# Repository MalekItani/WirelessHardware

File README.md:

# Wireless Hardware
Welcome to the repository containing the circuit design files for wireless earbuds! In this repository, you will find all the necessary files to create your own wireless earbuds, including schematics, PCB layouts, and bill of materials.

## Software Dependencies/Requirements

- Kicad version 4.0 or greater.

## Repository Contents
This repository contains the following directories:

**Schematics**: Detailed diagrams of the circuitry used in the wireless earbuds.

**PCB layouts**: Physical layouts of the printed circuit board used in the wireless earbuds.

**Bill of materials**: A list of components and materials needed to build the wireless earbuds.

## Getting Started
To use these circuit design files, follow the steps below:

#### 1. Install KiCad: 
Download and install KiCad version 4.0 or greater from the official website. Choose the appropriate version for your operating system.

#### 2. Customize and Optimize: 
Import the schematics and PCB layouts into KiCad to begin customizing and optimizing the design to fit your specific needs. For detailed instructions on using KiCad, consult the official documentation.

## Firmware
The repository containing the firmware is located here: [https://github.com/antoniog11/OAEbud-firmware](https://github.com/antoniog11/OAEbud-firmware/)

## License
This repository is licensed under the MIT License. You are free to use and modify the circuit design files in any way you see fit, as long as you include the appropriate attribution and comply with the terms of the license.

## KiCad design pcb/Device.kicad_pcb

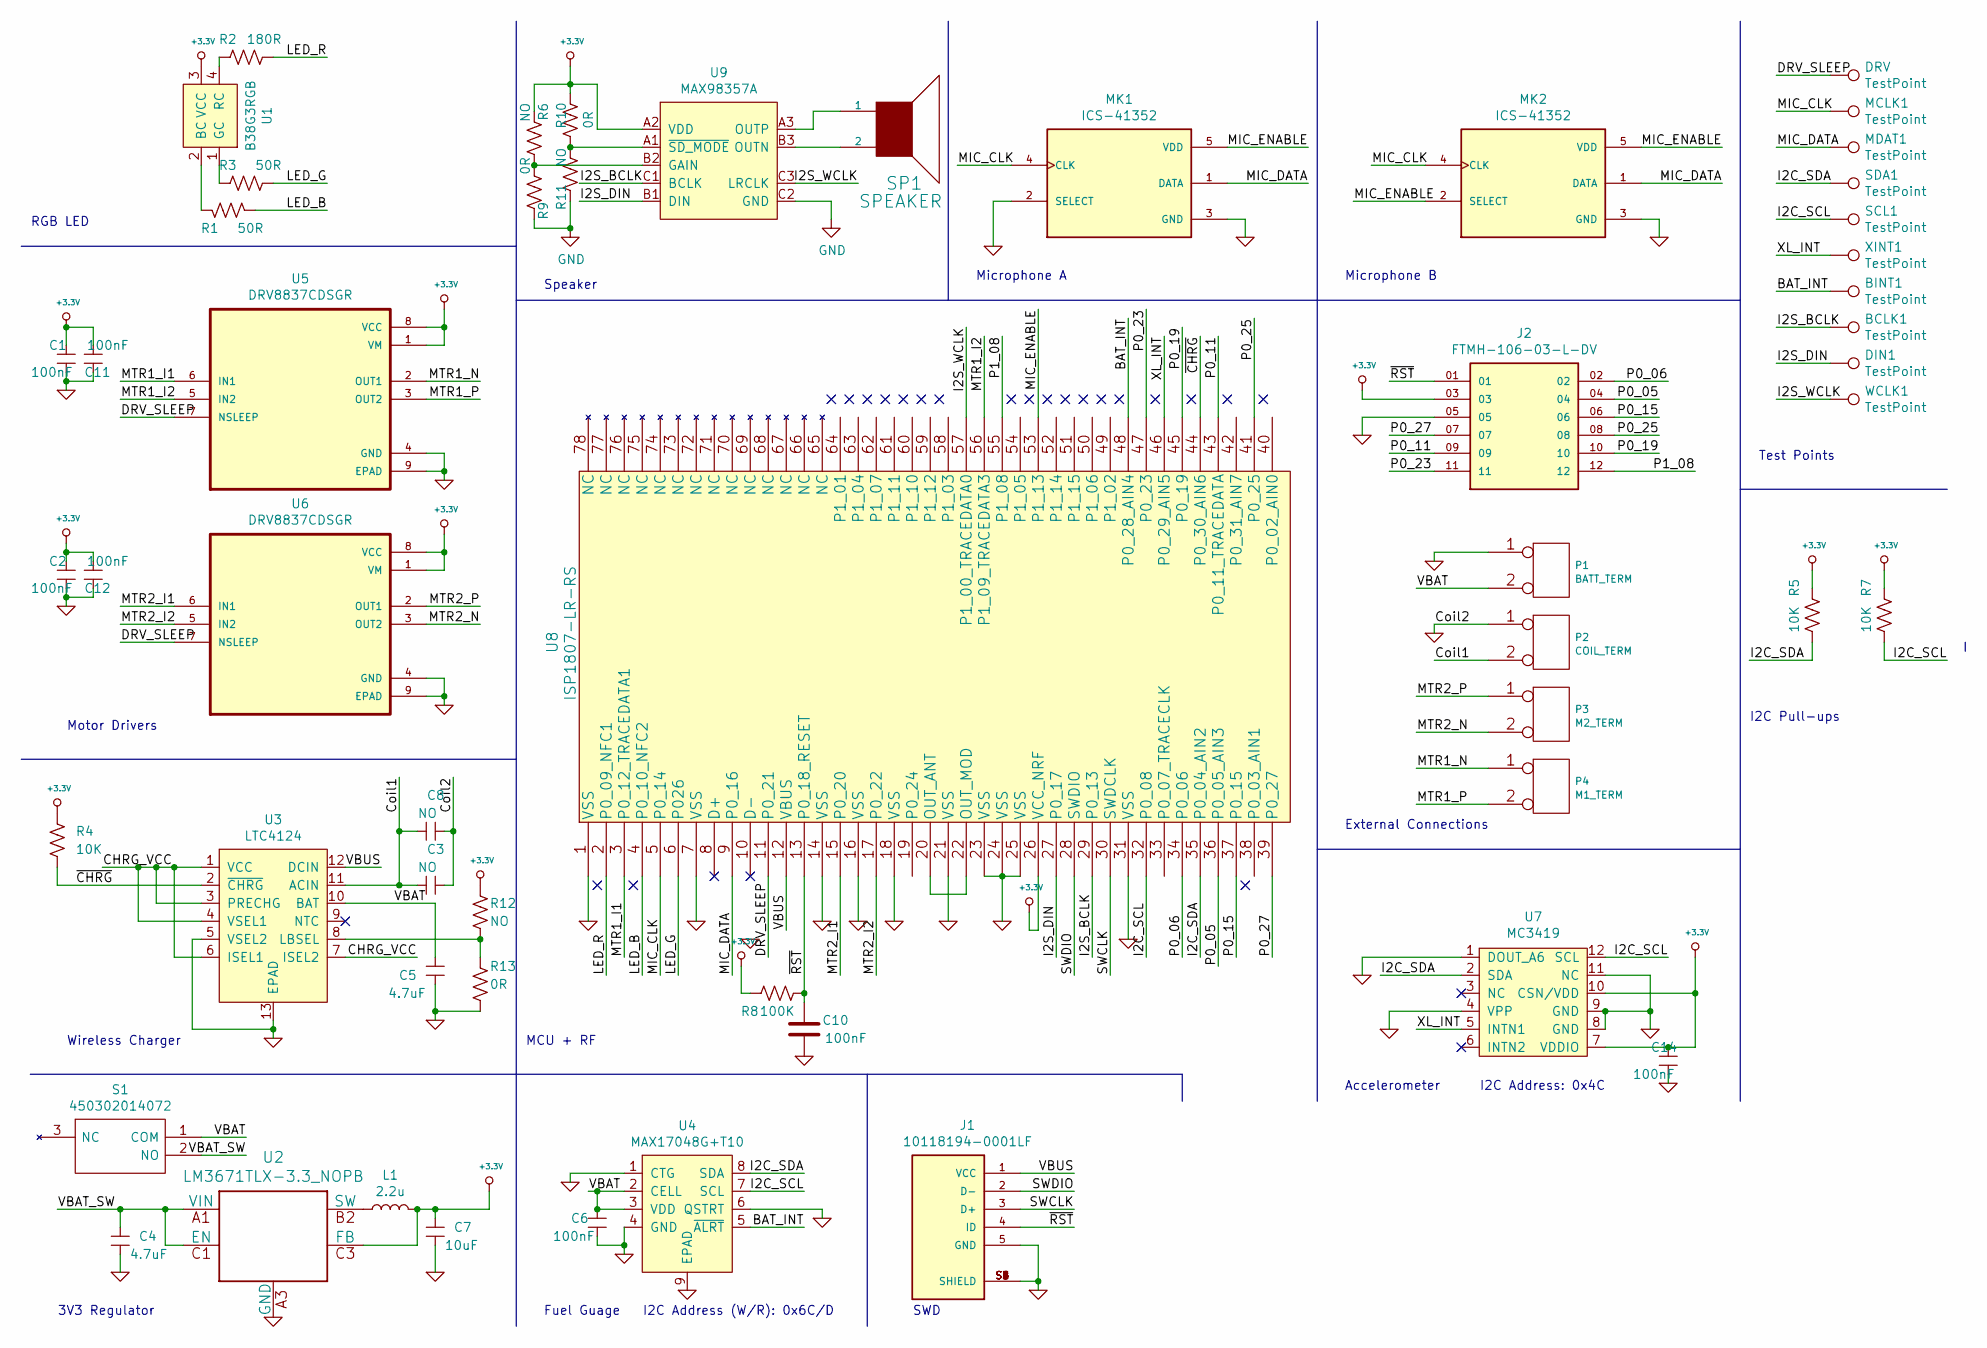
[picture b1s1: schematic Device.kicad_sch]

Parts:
BCLK1: TestPoint; TestPoint_Pad_D1.0mm
BINT1: TestPoint; TestPoint_Pad_D1.0mm
C1, C2, C6, C10, C11, C12, C14: 100nF; C_0402_1005Metric
C3, C8: NO; C_0402_1005Metric
C4, C5: 4.7uF; C_0603_1608Metric
C7: 10uF; C_0603_1608Metric
DIN1: TestPoint; TestPoint_Pad_D1.0mm
DRV: TestPoint; TestPoint_Pad_D1.0mm
J1: 10118194-0001LF; AMPHENOL_10118194-0001LF; PARTREV B
J2: FTMH-106-03-L-DV; SAMTEC_FTMH-106-03-L-DV; Manufacturer P/N FTMH-106-03-L-DV
L1: 2.2u; L_0805_2012Metric; Manufacturer P/N DFE201210U-2R2M=P2
MCLK1: TestPoint; TestPoint_Pad_D1.0mm
MDAT1: TestPoint; TestPoint_Pad_D1.0mm
MK1, MK2: ICS-41352; MIC_ICS-41350; Manufacturer P/N ICS-41352
P1: BATT_TERM; JST_ACH_BM02B-ACHSS-GAN-ETF_1x02-1MP_P1.20mm_Vertical; Manufacturer P/N BM02B-ACHSS-GAN-ETF(LF)(SN
P2: COIL_TERM; TestPoint_2Pads_Pitch2.54mm_Drill0.8mm
P3: M2_TERM; PinHeader_1x02_P1.27mm_Vertical
P4: M1_TERM; PinHeader_1x02_P1.27mm_Vertical
R1, R3: 50R; R_0402_1005Metric
R2: 180R; R_0402_1005Metric
R4, R5, R7: 10K; R_0402_1005Metric
R6, R11, R12: NO; R_0402_1005Metric
R8: 100K; R_0402_1005Metric
R9, R10, R13: 0R; R_0402_1005Metric
S1: 450302014072; Manufacturer P/N 450302014072
SCL1: TestPoint; TestPoint_Pad_D1.0mm
SDA1: TestPoint; TestPoint_Pad_D1.0mm
SP1: SPEAKER; CUI_CMT-4023S-SMT-TR; Manufacturer P/N SMT-0440-T-HT-R
U1: B38G3RGB; B38G3RGB10D0003H2U1930; Manufacturer P/N B38G3RGB-10D0003H2U1930
U2: LM3671TLX-3.3_NOPB; LM3671TLX-3.3&slash_NOPB; Manufacturer P/N LM3671TLX-3.3/NOPB
U3: LTC4124; LTC4124EV-TRMPBF; Manufacturer P/N LTC4124EV#TRMPBF
U4: MAX17048G+T10; SON50P200X200X80-9N; Manufacturer P/N MAX17048G+T10
U5, U6: DRV8837CDSGR; SON50P200X200X80-9N; Manufacturer P/N DRV8837CDSGR
U7: MC3419; LGA-12_2x2mm_P0.5mm; Manufacturer P/N MC3419
U8: ISP1807-LR-RS; Manufacturer P/N ISP1807-LR-RS
U9: MAX98357A; Maxim_WLP-9_1.595x1.415_Layout3x3_P0.4mm_Ball0.27mm_Pad0.25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; Manufacturer P/N MAX98357AEWL+T
WCLK1: TestPoint; TestPoint_Pad_D1.0mm
XINT1: TestPoint; TestPoint_Pad_D1.0mm

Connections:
+3.3V: C1.1, C2.1, C7.2, C11.2, C12.2, C14.1, J2.03, L1.2, R4.1, R5.1, R6.2, R7.1, R8.1, R10.1, R12.1, U1.3 (VCC), U2.C3 (FB), U5.1 (VM), U5.8 (VCC), U6.1 (VM), U6.8 (VCC), U7.7 (VDDIO), U7.10 (CSN/VDD), U8.26 (VCC_NRF), U9.A2 (VDD)
/BAT_INT: BINT1.1, U4.5 (~ALRT), U8.48 (P0_28_AIN4)
/CHRG_VCC: U3.1 (VCC), U3.3 (PRECHG), U3.4 (VSEL1), U3.6 (ISEL1), U3.7 (ISEL2)
/Coil1: C3.2, C8.2, P2.2 (PM), U3.11 (ACIN)
/DRV_SLEEP: DRV.1, U5.7 (NSLEEP), U6.7 (NSLEEP), U8.11 (P0_21); also elsewhere on the board
/I2C_SCL: R7.2, SCL1.1, U4.7 (SCL), U7.12 (SCL), U8.32 (P0_08)
/I2C_SDA: R5.2, SDA1.1, U4.8 (SDA), U7.2 (SDA), U8.35 (P0_04_AIN2)
/I2S_BCLK: BCLK1.1, U8.29 (P0_13), U9.C1 (BCLK)
/I2S_DIN: DIN1.1, U8.27 (P0_17), U9.B1 (DIN)
/I2S_WCLK: U8.57 (P1_00_TRACEDATA0), U9.C3 (LRCLK), WCLK1.1
/LED_B: R1.2, U8.4 (P0_10_NFC2)
/LED_G: R3.2, U8.6 (P026)
/LED_R: R2.2, U8.2 (P0_09_NFC1)
/MIC_CLK: MCLK1.1, MK1.4 (CLK), MK2.4 (CLK), U8.5 (P0_14)
/MIC_DATA: MDAT1.1, MK1.1 (DATA), MK2.1 (DATA), U8.9 (P0_16)
/MIC_ENABLE: MK1.5 (VDD), MK2.2 (SELECT), MK2.5 (VDD), U8.53 (P1_13)
/MTR1_I1: U5.6 (IN1), U8.3 (P0_12_TRACEDATA1)
/MTR1_I2: U5.5 (IN2), U8.56 (P1_09_TRACEDATA3)
/MTR1_N: P4.1, U5.2 (OUT1)
/MTR1_P: P4.2 (PM), U5.3 (OUT2)
/MTR2_I1: U6.6 (IN1), U8.15 (P0_20)
/MTR2_I2: U6.5 (IN2), U8.17 (P0_22)
/MTR2_N: P3.2 (PM), U6.3 (OUT2)
/MTR2_P: P3.1, U6.2 (OUT1)
/P0_05: J2.04, U8.36 (P0_05_AIN3)
/P0_06: J2.02, U8.34 (P0_06)
/P0_11: J2.09, U8.43 (P0_11_TRACEDATA)
/P0_15: J2.06, U8.37 (P0_15)
/P0_19: J2.10, U8.45 (P0_19)
/P0_23: J2.11, U8.47 (P0_23)
/P0_25: J2.08, U8.41 (P0_25)
/P0_27: J2.07, U8.39 (P0_27)
/P1_08: J2.12, U8.55 (P1_08)
/SWCLK: J1.3 (D+), U8.30 (SWDCLK)
/SWDIO: J1.2 (D-), U8.28 (SWDIO)
/VBAT: C5.1, C6.2, P1.2 (PM), S1.1 (COM), U3.10 (BAT), U4.2 (CELL), U4.3 (VDD)
/VBAT_SW: C4.2, S1.2 (NO), U2.A1 (VIN), U2.C1 (EN)
/VBUS: J1.1 (VCC), U3.12 (DCIN), U8.12 (VBUS)
/XL_INT: U7.5 (INTN1), U8.46 (P0_29_AIN5), XINT1.1
/~CHRG: R4.2, U3.2 (~CHRG), U8.44 (P0_30_AIN6)
/~RST: C10.1, J1.4 (ID), J2.01, R8.2, U8.13 (P0_18_RESET)
GND: C1.2, C2.2, C3.1, C4.1, C5.2, C6.1, C7.1, C8.1, C10.2, C11.1, C12.1, C14.2, J1.5 (GND), J1.S1 (SHIELD), J1.S2 (SHIELD), J1.S3 (SHIELD), J1.S4 (SHIELD), J1.S5 (SHIELD), J1.S6 (SHIELD), J2.05, MK1.2 (SELECT), MK1.3 (GND), MK2.3 (GND), P1.1, P2.1, R9.1, R11.1, R13.2, U2.A3 (GND), U3.5 (VSEL2), U3.13 (EPAD), U4.1 (CTG), U4.4 (GND), U4.6 (QSTRT), U4.9 (EPAD), U5.4 (GND), U5.9 (EPAD), U6.4 (GND), U6.9 (EPAD), U7.1 (DOUT_A6), U7.4 (VPP), U7.8 (GND), U7.9 (GND), U7.11 (NC), U8.1 (VSS), U8.7 (VSS), U8.14 (VSS), U8.16 (VSS), U8.18 (VSS), U8.21 (VSS), U8.23 (VSS), U8.24 (VSS), U8.25 (VSS), U8.31 (VSS), U9.C2 (GND)
unnamed: L1.1, U2.B2 (SW)
unnamed: R1.1, U1.2 (BC)
unnamed: R2.1, U1.4 (RC)
unnamed: R3.1, U1.1 (GC)
unnamed: R6.1, R9.2, U9.B2 (GAIN)
unnamed: R10.2, R11.2, U9.A1 (~SD_MODE)
unnamed: R12.2, R13.1, U3.8 (LBSEL)
unnamed: SP1.1, U9.A3 (OUTP)
unnamed: SP1.2, U9.B3 (OUTN)
unnamed: U8.20 (OUT_ANT), U8.22 (OUT_MOD)

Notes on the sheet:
3V3 Regulator
I2C Pull-ups
Test Points
Wireless Charger
SWD
MCU + RF
RGB LED
Motor Drivers
Speaker
Fuel Guage
Microphone B
External Connections
Accelerometer
Microphone A
I2C Address: 0x4C
I2C Address (W/R): 0x6C/D

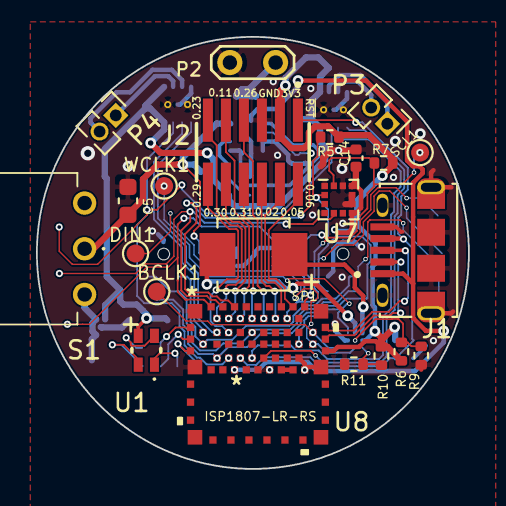
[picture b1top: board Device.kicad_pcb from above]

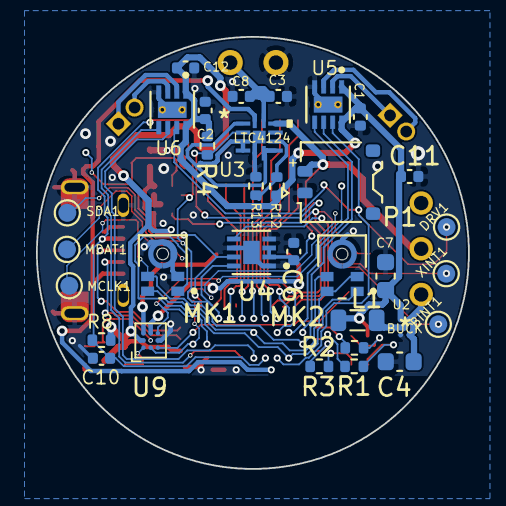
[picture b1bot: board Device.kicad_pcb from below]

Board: 2 copper layers, 24.0 x 24.0 mm, 55 parts (33 on the bottom side), 52 nets.

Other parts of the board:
DRV1: TestPoint; TestPoint_Pad_D1.0mm

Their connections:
/DRV_SLEEP: DRV1.1; also elsewhere on the board

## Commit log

2023-04-11 Added BOM
2023-04-11 Removed
2023-04-11 Updated speaker

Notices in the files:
parts and their libraries:
Copyright 2021 Accelerated Designs. All rights reserved.
